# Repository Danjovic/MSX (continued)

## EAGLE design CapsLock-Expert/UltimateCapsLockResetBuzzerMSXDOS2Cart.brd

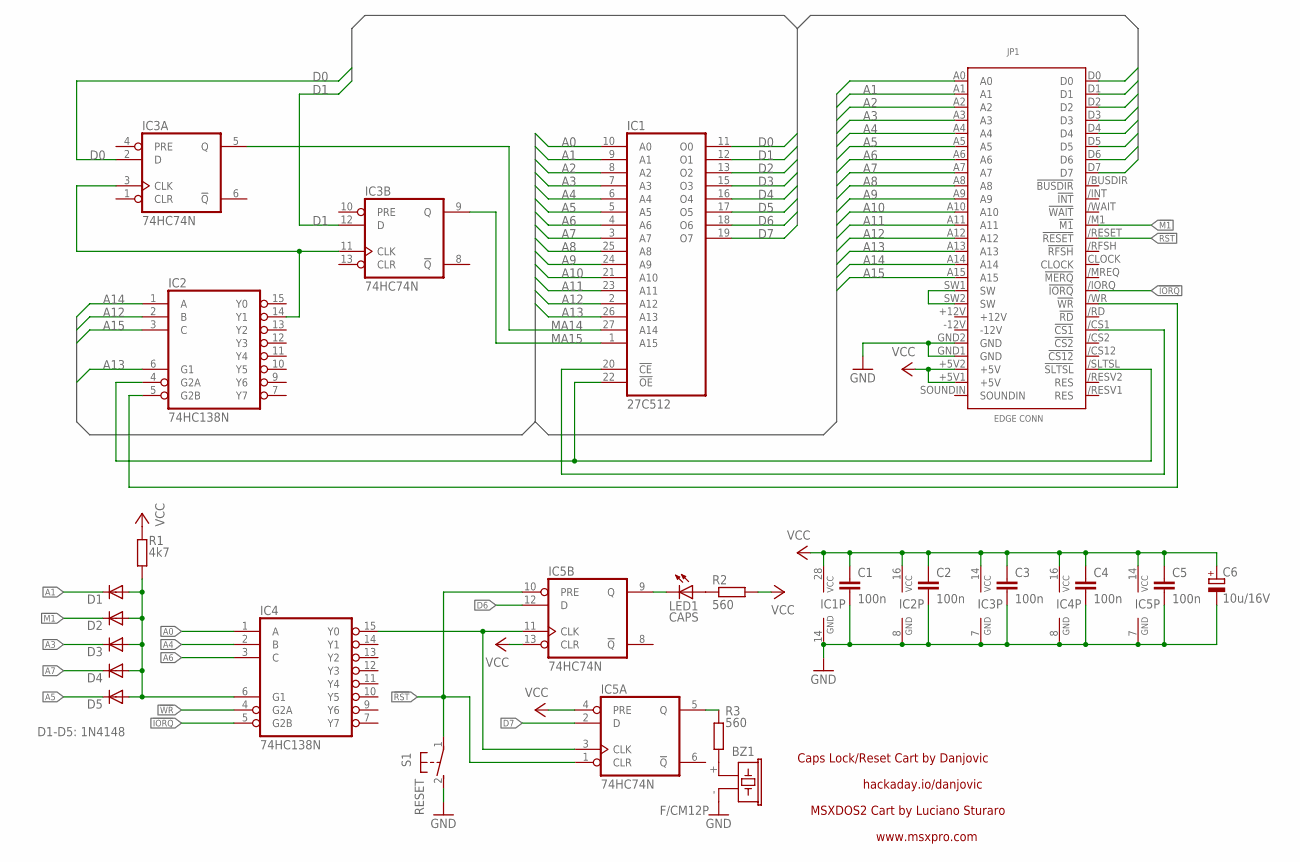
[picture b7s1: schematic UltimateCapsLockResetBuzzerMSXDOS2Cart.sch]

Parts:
BZ1: F/CM12P
C1, C2, C3, C4, C5: 100n; C050-030X075
C6: 10u/16V; E2,5-5
D1, D2, D3, D4, D5: DIODE-D-5; D-5
IC1: 27C512; DIL28
IC2, IC4: 74HC138N; DIL16
IC3, IC5: 74HC74N; DIL14
JP1: MSXCART; PATOLA-MSX
LED1: CAPS; Q62902-B155
R1: 4k7; 0204/5
R2, R3: 560; 0204/5
S1: RESET; B3F-31XX

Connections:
!CS1: IC1.20 (!CE), JP1./CS1 (!CS1)
!IORQ: IC4.5 (G2B), JP1./IORQ (!IORQ)
!M1: D2.C, JP1./M1 (!M1)
!RST: IC5.1 (CLR), IC5.10 (PRE), JP1./RESET (!RESET), S1.1
!SLTSL: IC1.22 (!OE), IC2.4 (G2A), JP1./SLTSL (!SLTSL)
!WR: IC2.5 (G2B), IC4.4 (G2A), JP1./WR (!WR)
A0: IC1.10 (A0), IC4.1 (A), JP1.A0
A1: D1.C, IC1.9 (A1), JP1.A1
A2: IC1.8 (A2), JP1.A2
A3: D3.C, IC1.7 (A3), JP1.A3
A4: IC1.6 (A4), IC4.2 (B), JP1.A4
A5: D5.C, IC1.5 (A5), JP1.A5
A6: IC1.4 (A6), IC4.3 (C), JP1.A6
A7: D4.C, IC1.3 (A7), JP1.A7
A8: IC1.25 (A8), JP1.A8
A9: IC1.24 (A9), JP1.A9
A10: IC1.21 (A10), JP1.A10
A11: IC1.23 (A11), JP1.A11
A12: IC1.2 (A12), IC2.2 (B), JP1.A12
A13: IC1.26 (A13), IC2.6 (G1), JP1.A13
A14: IC2.1 (A), JP1.A14
A15: IC2.3 (C), JP1.A15
D0: IC1.11 (O0), IC3.2 (D), JP1.D0
D1: IC1.12 (O1), IC3.12 (D), JP1.D1
D2: IC1.13 (O2), JP1.D2
D3: IC1.15 (O3), JP1.D3
D4: IC1.16 (O4), JP1.D4
D5: IC1.17 (O5), JP1.D5
D6: IC1.18 (O6), IC5.12 (D), JP1.D6
D7: IC1.19 (O7), IC5.2 (D), JP1.D7
GND: BZ1.- (2), C1.2, C2.2, C3.2, C4.2, C5.2, C6.-, IC1.14 (GND), IC2.8 (GND), IC3.7 (GND), IC4.8 (GND), IC5.7 (GND), JP1.GND1 (GND), JP1.GND2 (GND), S1.2 (S)
MA14: IC1.27 (A14), IC3.5 (Q)
MA15: IC1.1 (A15), IC3.9 (Q)
unnamed: IC5.9 (Q), LED1.K (C)
unnamed: IC2.14 (Y1), IC3.3 (CLK), IC3.11 (CLK)
unnamed: LED1.A, R2.1
unnamed: IC5.5 (Q), R3.1
unnamed: IC4.15 (Y0), IC5.3 (CLK), IC5.11 (CLK)
unnamed: BZ1.+ (1), R3.2
unnamed: D1.A, D2.A, D3.A, D4.A, D5.A, IC4.6 (G1), R1.2
SW1-2: JP1.SW1 (SW), JP1.SW2 (SW)
VCC: C1.1, C2.1, C3.1, C4.1, C5.1, C6.+, IC1.28 (VCC), IC2.16 (VCC), IC3.14 (VCC), IC4.16 (VCC), IC5.4 (PRE), IC5.13 (CLR), IC5.14 (VCC), JP1.+5V1 (+5V), JP1.+5V2 (+5V), R1.1, R2.2

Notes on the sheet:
MSXDOS2 Cart by Luciano Sturaro
www.msxpro.com
Caps Lock/Reset Cart by Danjovic
hackaday.io/danjovic
D1-D5: 1N4148

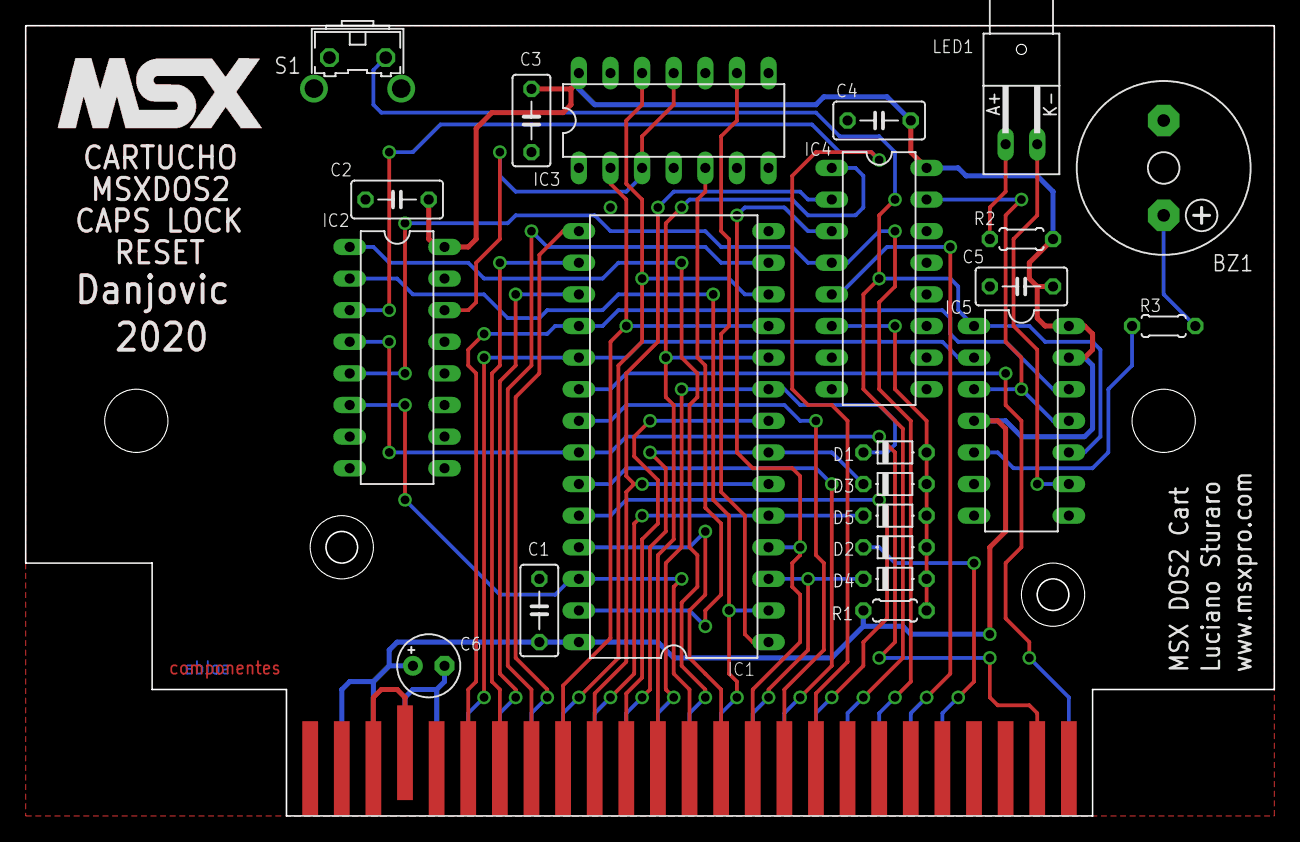
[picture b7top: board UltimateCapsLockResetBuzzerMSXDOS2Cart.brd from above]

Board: 2 copper layers, 100.3 x 63.5 mm, 23 parts (0 on the bottom side), 42 nets.

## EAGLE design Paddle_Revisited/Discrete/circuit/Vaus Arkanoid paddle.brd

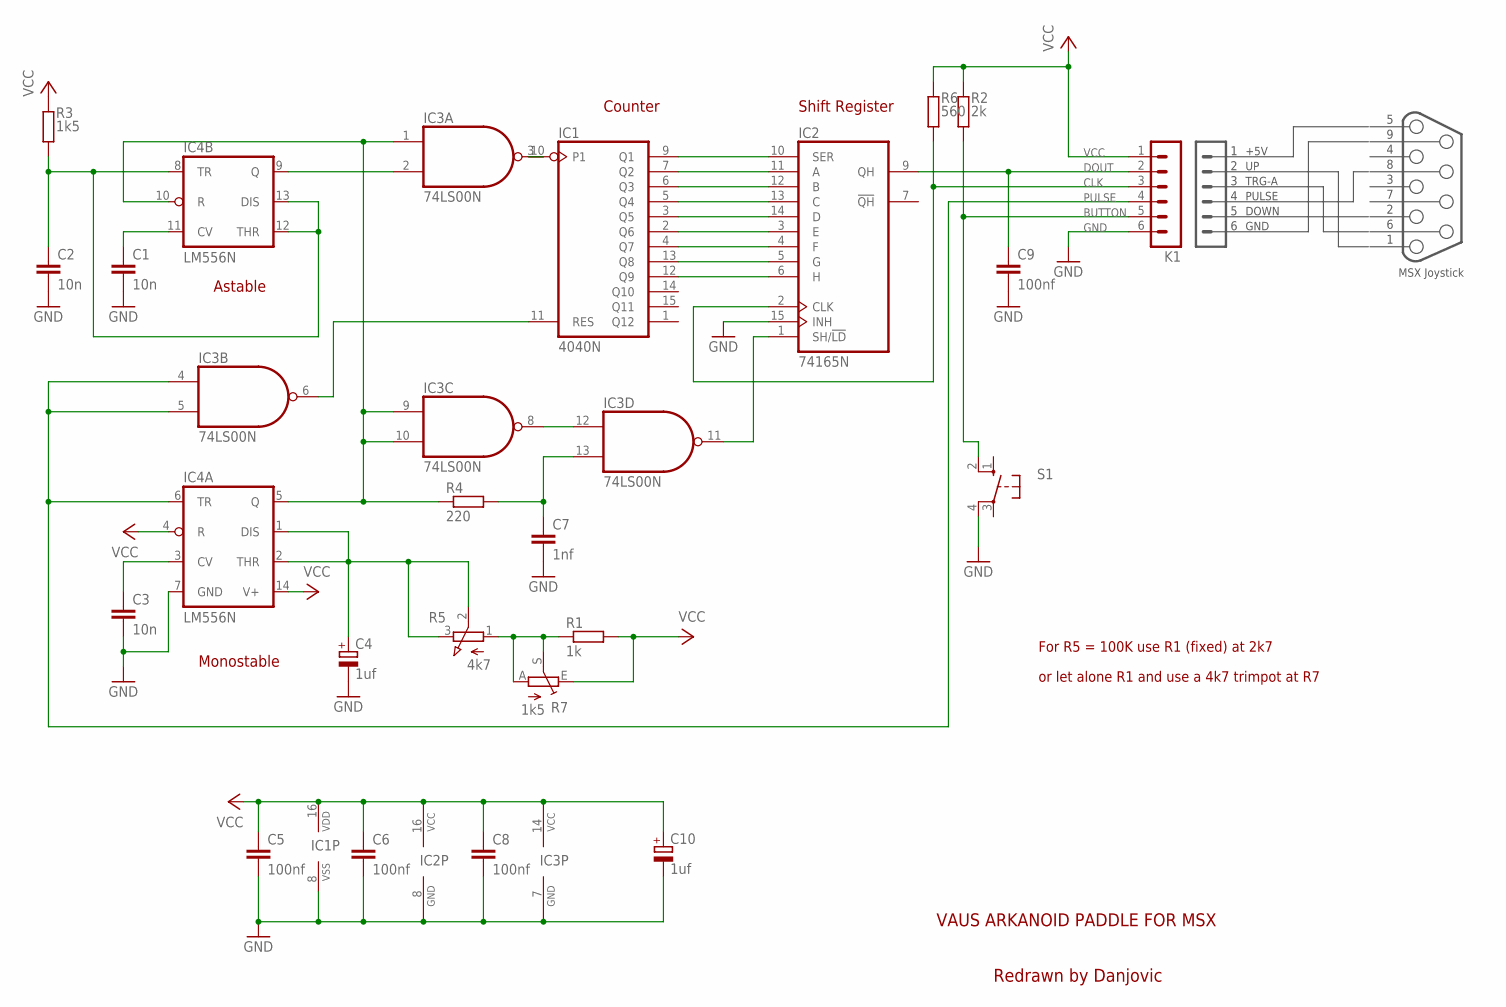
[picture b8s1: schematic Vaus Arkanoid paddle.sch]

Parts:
C1, C2, C3: 10n; C050-024X044
C4, C10: 1uf; E2-4
C5, C6, C8, C9: 100nf; C050-024X044
C7: 1nf; C050-024X044
IC1: 4040N; DIL16
IC2: 74165N; DIL16
IC3: 74LS00N; DIL14
IC4: LM556N; DIL14
K1: MA06-1
R1: 1k; 0207/7
R2: 2k; 0207/7
R3: 1k5; 0207/7
R4: 220; 0207/7
R5: 4k7; 3RP/1610N_THRU
R6: 560; 0207/7
R7: 1k5; CT6
S1: 40-XX; B3F-40XX

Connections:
BUTTON: K1.5, R2.1, S1.2 (S1)
CLK: IC2.2 (CLK), K1.3, R6.1
DOUT: C9.1, IC2.9 (QH), K1.2
GND: C1.2, C2.2, C3.2, C4.-, C5.2, C6.2, C7.2, C8.2, C9.2, C10.-, IC1.8 (VSS), IC2.8 (GND), IC2.15 (INH), IC3.7 (GND), IC4.7 (GND), K1.6, S1.4 (P1)
unnamed: IC2.1 (SH/!LD), IC3.11 (O)
unnamed: IC1.2 (Q6), IC2.3 (E)
unnamed: IC1.4 (Q7), IC2.4 (F)
unnamed: IC1.13 (Q8), IC2.5 (G)
unnamed: IC1.12 (Q9), IC2.6 (H)
unnamed: IC1.9 (Q1), IC2.10 (SER)
unnamed: IC1.7 (Q2), IC2.11 (A)
unnamed: IC1.6 (Q3), IC2.12 (B)
unnamed: IC1.5 (Q4), IC2.13 (C)
unnamed: IC1.3 (Q5), IC2.14 (D)
unnamed: IC3.8 (O), IC3.12 (I0)
unnamed: IC3.1 (I0), IC3.9 (I0), IC3.10 (I1), IC4.5 (Q), IC4.10 (R), R4.1
unnamed: C7.1, IC3.13 (I1), R4.2
unnamed: C2.1, IC4.8 (TR), IC4.12 (THR), IC4.13 (DIS), R3.1
unnamed: R1.1, R5.1 (A), R7.A, R7.S
unnamed: IC1.11 (RES), IC3.6 (O)
unnamed: IC1.10 (P1), IC3.3 (O)
unnamed: IC3.2 (I1), IC4.9 (Q)
unnamed: C4.+, IC4.1 (DIS), IC4.2 (THR), R5.2 (S), R5.3 (E)
unnamed: C1.1, IC4.11 (CV)
unnamed: C3.1, IC4.3 (CV)
PULSE: IC3.4 (I0), IC3.5 (I1), IC4.6 (TR), K1.4
VCC: C5.1, C6.1, C8.1, C10.+, IC1.16 (VDD), IC2.16 (VCC), IC3.14 (VCC), IC4.4 (R), IC4.14 (V+), K1.1, R1.2, R2.2, R3.2, R6.2, R7.E

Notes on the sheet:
DOWN
TRG-A
PULSE
+5V
GND
MSX Joystick
Monostable
Astable
Counter
Shift Register
VAUS ARKANOID PADDLE FOR MSX
Redrawn by Danjovic
For R5 = 100K use R1 (fixed) at 2k7
or let alone R1 and use a 4k7 trimpot at R7

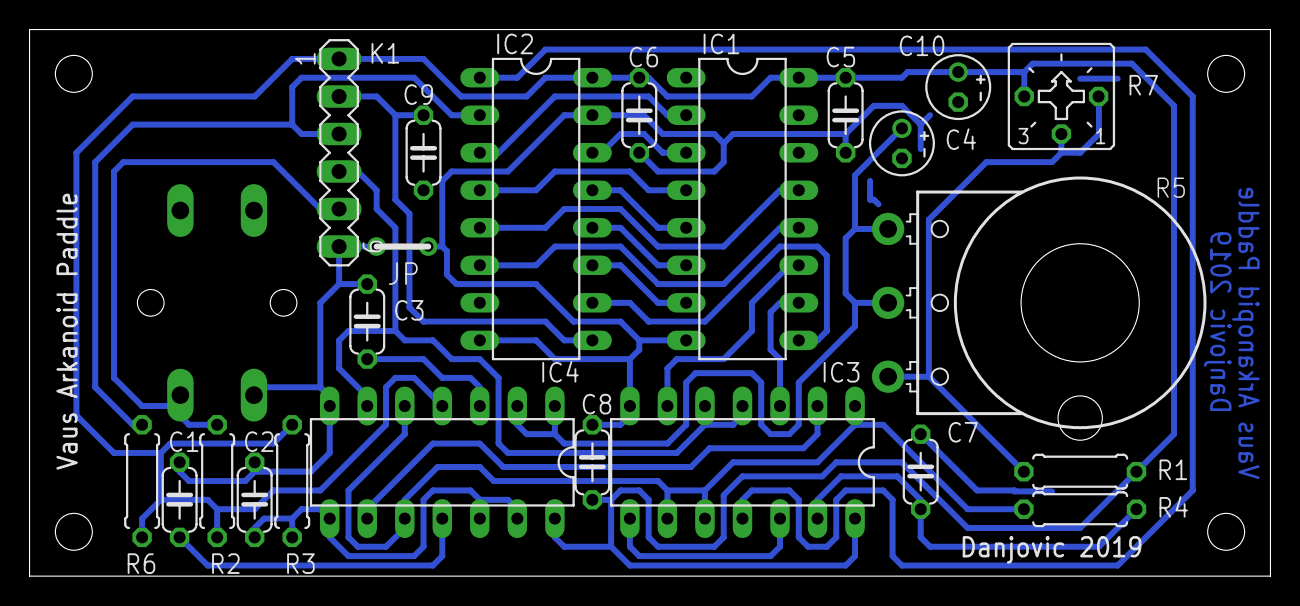
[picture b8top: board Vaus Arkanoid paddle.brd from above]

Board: 2 copper layers, 84.0 x 37.0 mm, 24 parts (1 on the bottom side), 27 nets.

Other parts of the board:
U$1: CP-011

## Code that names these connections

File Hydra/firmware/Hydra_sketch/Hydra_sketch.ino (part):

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
Arduino
/AVR    Function
 0/PD0  Nintendo 64 1 wire Clock/Data
 1/PD1  TXD for serial debug             
 2/PD2  MSX Pulse input (INT0)             
 3/PD3  Dualshock ATT / SNES Latch / Shift Register Latch (Sega) 
 4/PD4  Dualshock CLK / SNES Clock / Shift Register Clock (Sega) 
 5/PD5  Dualshock CMD /            / Sega SELECT    
 6/PD6  Dualshock DATA      
 7/PD7  Dualshock ACK     
 8/PB0  MSX UP    (output)           
 9/PB1  MSX DOWN  (output)             
10/PB2  MSX LEFT  (output)             
11/PB3  MSX RIGHT (output)             
12/PB4  MSX TRGA  (output)            
13/PB5  MSX TRGB  (output)             
A0/PC0  Shift Register Data (Sega)   
A1/PC1  SNES Data   
A2/PC2  Mouse DAT           
A3/PC3  Mouse CLK           
A4/PC4  OLED display I2C SCL / WII nunchuck I2C SCL       
A5/PC5  OLED display I2C SDA / WII nunchuck I2C SDA      
*/
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#define mdTRACKBALL         5  // 5 = Trackball
#define mdTOUCHPAD          6  // 6 = Touchpad

#define JoyPin1  8 // PB0 UP
#define JoyPin2  9 // PB1 DOWN
#define JoyPin3 10 // PB2 LEFT
#define JoyPin4 11 // PB3 RIGHT
#define JoyPin6 12 // PB4 TRIGGER A
#define JoyPin7 13 // PB5 TRIGGER B
#define JoyPin8  2 // PD2 PULSE
long time; // No C


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// Nintendo 64 device library by NicoHood
// https://www.github.com/NicoHood/Nintendo
#include "Nintendo.h"
#define N64 0   // PD0
#define GCUBE 7 // PD7
CN64Controller N64Controller(N64);// Define a N64 Controller
CGamecubeController GamecubeController(GCUBE);// Define a Gamecube Controller

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#define MSX_PORT PORTB
#define MSX_DDR  DDRB

#define MSX_UP    0  // PB0
#define MSX_DOWN  1  // PB1
#define MSX_LEFT  2  // PB2
#define MSX_RIGHT 3  // PB3
#define MSX_TRGA  4  // PB4
#define MSX_TRGB  5  // PB5

//uint8_t msx_buttons  = 0xff;  // no button pressed
static volatile uint8_t msx_paddle_1_2   = 0; // Pin 1 - UP      
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  temp = ps2x.readType();

  if (temp==1) {  // Dualshock
    ps2x.read_gamepad(false, 0); //read controller and set large motor to spin at 'vibrate' speed
    if(ps2x.Button(PSB_GREEN)) return DUALSHOCK;  // triangle is A button 
    
    } else if (temp==2) {  // Guitar
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
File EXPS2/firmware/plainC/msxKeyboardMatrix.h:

//    _____  _____  ___   _____
//   | __\ \/ / _ \/ __| / /_  )
//   | _| >  <|  _/\__ \/ / / /
//   |___/_/\_\_|  |___/_/ /___|
//
//   Teclado PS/2 externo para Expert XP800

// Conexao dos pinos do AVR com a PPI
// AVR interface pin assignment to the PPI

// AVR  PPI

// PC0  PC0   /   sel A
// PC1  PC1   /   sel B
// PC2  PC2   /   sel C
// PC3  PC3   /   sel D

// PD0  PB5   /   X5
// PD1  PB0   /   X0
// PD2  PB6   /   X6
// PD3  PB2   /   X2
// PD4  PB7   /   X7
// PD5  PB4   /   X4
// PD6  PB1   /   X1
// PD7  PB3   /   X3

/*
SH  ROW[0..10] COL [0..7]

    7     6     5     4     3     2     1     0    BIT
 +-----------------------------------------------+
 |SHIFT|       ROW [0..10]     |    COL[0..7]    |
 +-----------------------------------------------+


    7     6     5     4     3     2     1     0    BIT
 +-----------------------------------------------+
 |  7  |  5  |  6  |  4  |  3  |  2  |  1  |  0  |   Row 0
 +-----+-----+-----+-----+-----+-----+-----+-----|
 |  ;  |  [  |  ]  |  \  |  =  |  -  |  9  |  8  |   Row 1
 +-----+-----+-----+-----+-----+-----+-----+-----|
 |  B  |  |  |  A  |  /  |  .  |  ,  |  `  |  '  |   Row 2
 +-----+-----+-----+-----+-----+-----+-----+-----|
 |  J  |  H  |  I  |  G  |  F  |  E  |  D  |  C  |   Row 3
 +-----+-----+-----+-----+-----+-----+-----+-----|
 |  R  |  P  |  Q  |  O  |  N  |  M  |  L  |  K  |   Row 4
 +-----+-----+-----+-----+-----+-----+-----+-----|
 |  Z  |  X  |  Y  |  W  |  V  |  U  |  T  |  S  |   Row 5
 +-----+-----+-----+-----+-----+-----+-----+-----|
 | F3  | F1  | F2  |CODE | CAP |GRAPH|CTRL |SHIFT|   Row 6
 +-----+-----+-----+-----+-----+-----+-----+-----|
 | CR  | BS  | SEL |STOP | TAB | ESC | F5  | F4  |   Row 7
 +-----+-----+-----+-----+-----+-----+-----+-----|
 |RIGHT| UP  |DOWN |LEFT | DEL | INS |HOME |SPACE|   Row 8
 +-----+-----+-----+-----+-----+-----+-----+-----|
 | KP4 | KP2 | KP2 | KP1 | KP0 |NUM/ |NUM+ |NUM* |   Row 9
 +-----+-----+-----+-----+-----+-----+-----+-----|
 |  .  |  -  |  ,  | KP9 | KP8 | KP7 | KP6 | KP5 |   Row 10
 +-----------------------------------------------+
    7     5     6     4     3     2     1     0       Column

*/

// Mapa das linhas de selecao da PPI
// PPI selection line mapping
//      line bit
#define selA  0
#define selB  1
#define selC  2
#define selD  3


#define row0  ( (0<<selD)|(0<<selC)|(0<<selB)|(0<<selA) ) <<3
#define row1  ( (0<<selD)|(0<<selC)|(0<<selB)|(1<<selA) ) <<3
#define row2  ( (0<<selD)|(0<<selC)|(1<<selB)|(0<<selA) ) <<3
#define row3  ( (0<<selD)|(0<<selC)|(1<<selB)|(1<<selA) ) <<3
#define row4  ( (0<<selD)|(1<<selC)|(0<<selB)|(0<<selA) ) <<3
#define row5  ( (0<<selD)|(1<<selC)|(0<<selB)|(1<<selA) ) <<3
#define row6  ( (0<<selD)|(1<<selC)|(1<<selB)|(0<<selA) ) <<3
#define row7  ( (0<<selD)|(1<<selC)|(1<<selB)|(1<<selA) ) <<3
#define row8  ( (1<<selD)|(0<<selC)|(0<<selB)|(0<<selA) ) <<3
#define row9  ( (1<<selD)|(0<<selC)|(0<<selB)|(1<<selA) ) <<3
#define rowA  ( (1<<selD)|(0<<selC)|(1<<selB)|(0<<selA) ) <<3
#define rowB  ( (1<<selD)|(0<<selC)|(1<<selB)|(1<<selA) ) <<3
#define rowC  ( (1<<selD)|(1<<selC)|(0<<selB)|(0<<selA) ) <<3
#define rowD  ( (1<<selD)|(1<<selC)|(0<<selB)|(1<<selA) ) <<3
#define rowE  ( (1<<selD)|(1<<selC)|(1<<selB)|(0<<selA) ) <<3
#define rowF  ( (1<<selD)|(1<<selC)|(1<<selB)|(1<<selA) ) <<3


// Posicao das bits das colunas (teclas)
// Column position bit mapping (keys)
//   column  bit
#define col0  5
#define col1  0
#define col2  6
#define col3  2
#define col4  7
#define col5  4
#define col6  1
#define col7  3


//  SHIFT Position in Matrx
#define LIN_SHIFT 6
#define COL_SHIFT col0


#define _NONE          0x7F
#define _SH            0x80

#define _0            ( row0 | col0 )
#define _1            ( row0 | col1 )
#define _2            ( row0 | col2 )
#define _3            ( row0 | col3 )
#define _4            ( row0 | col4 )
#define _5            ( row0 | col5 )
#define _6            ( row0 | col6 )
#define _7            ( row0 | col7 )

#define _8            ( row1 | col0 )
#define _9            ( row1 | col1 )
#define _MINUS        ( row1 | col2 )
#define _EQUAL        ( row1 | col3 )
#define _OPENBRACKET  ( row1 | col4 )
#define _ACUTE        ( row1 | col5 )
#define _OPENKEY      ( row1 | col6 )
#define _TILDE        ( row1 | col7 )

#define _ASTERISK     ( row2 | col0 )
#define _CCEDIL       ( row2 | col1 )
#define _COMMA        ( row2 | col2 )
#define _DOT          ( row2 | col3 )
#define _SEMICOLON    ( row2 | col4 )
#define _SLASH        ( row2 | col5 )
#define _A            ( row2 | col6 )
#define _B            ( row2 | col7 )

#define _C            ( row3 | col0 )
#define _D            ( row3 | col1 )
#define _E            ( row3 | col2 )
#define _F            ( row3 | col3 )
#define _G            ( row3 | col4 )
#define _H            ( row3 | col5 )
#define _I            ( row3 | col6 )
#define _J            ( row3 | col7 )

#define _K            ( row4 | col0 )
#define _L            ( row4 | col1 )
#define _M            ( row4 | col2 )
#define _N            ( row4 | col3 )
#define _O            ( row4 | col4 )
#define _P            ( row4 | col5 )
#define _Q            ( row4 | col6 )
#define _R            ( row4 | col7 )

#define _S            ( row5 | col0 )
#define _T            ( row5 | col1 )
#define _U            ( row5 | col2 )
#define _V            ( row5 | col3 )
#define _W            ( row5 | col4 )
#define _X            ( row5 | col5 )
#define _Y            ( row5 | col6 )
#define _Z            ( row5 | col7 )

#define _SHIFT        ( row6 | col0 )
#define _CONTROL      ( row6 | col1 )
#define _GRAPH        ( row6 | col2 )
#define _CAPS         ( row6 | col3 )
#define _CODE         ( row6 | col4 )
#define _F1           ( row6 | col5 )
#define _F2           ( row6 | col6 )
#define _F3           ( row6 | col7 )

#define _F4           ( row7 | col0 )
#define _F5           ( row7 | col1 )
#define _ESC          ( row7 | col2 )
#define _TAB          ( row7 | col3 )
#define _STOP         ( row7 | col4 )
#define _BACKSPACE    ( row7 | col5 )
#define _SELECT       ( row7 | col6 )
#define _ENTER        ( row7 | col7 )

#define _SPACE        ( row8 | col0 )
#define _HOME         ( row8 | col1 )
#define _INSERT       ( row8 | col2 )
#define _DELETE       ( row8 | col3 )
#define _LEFT         ( row8 | col4 )
#define _UP           ( row8 | col5 )
#define _DOWN         ( row8 | col6 )
#define _RIGHT        ( row8 | col7 )

#define _KPPLUS       ( row9 | col0 )    
#define _KPMINUS      ( row9 | col1 )    
#define _KPTIMES      ( row9 | col2 )    
#define _KPSLASH      ( row9 | col3 )    

#define _KP1          ( _NONE       )    
#define _KP2          ( _NONE       )    
#define _KP3          ( _NONE       )    
#define _KP4          ( _NONE       )    

#define _KP5          ( _NONE       )    
#define _KP6          ( _NONE       )    
#define _KP7          ( _NONE       )    
#define _KP8          ( _NONE       )   
#define _KP9          ( _NONE       )       
#define _KPCOMMA      ( _NONE       )    
#define _KPDOT        ( _NONE       )    

// Shifted
#define _F6           ( _SH + _F1 )        // F6
#define _F7           ( _SH + _F2 )        // F7
#define _F8           ( _SH + _F3 )        // F8
#define _F9           ( _SH + _F4 )        // F9
#define _F10          ( _SH + _F5 )        // F10

#define _EXCLAMATION  ( _SH + _1  )         // !
#define _QUOTE        ( _SH + _2  )         // "
#define _NUMBER       ( _SH + _3  )         // #
#define _DOLLAR       ( _SH + _4  )         // $
#define _PERCENT      ( _SH + _5  )         // %
#define _POWER        ( _SH + _6  )         // ^
#define _AMPERSAND    ( _SH + _7  )         // &
#define _APOSTROPHE   ( _SH + _8  )         // '
#define _OPENBRACE    ( _SH + _9  )         // (
#define _CLOSEBRACE   ( _SH + _0  )         // )

#define _AT           ( _SH + _ASTERISK   ) // @
#define _UNDERSCORE   ( _SH + _MINUS      ) // _
#define _PLUS         ( _SH + _EQUAL      ) // +
#define _CLOSEKEY     ( _SH + _OPENKEY    ) // }

#define _GRAVE        ( _SH + _ACUTE      ) // `
#define _CLOSEBRACKET ( _SH + _OPENBRACKET) // ]
#define _CIRCUMFLEX   ( _SH + _TILDE      ) // ^

#define _LESSTHAN     ( _SH + _COMMA      ) // <
#define _GREATERTHAN  ( _SH + _DOT        ) // >
#define _COLON        ( _SH + _SEMICOLON  ) // :
#define _QUESTION     ( _SH + _SLASH      ) // ?

#define _PIPE         (  _NONE )

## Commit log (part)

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2016-10-28 Basic Release
2016-12-05 Add RESET switch and alternate LED/RESET mounting positons
2016-12-05 wrong name
2016-12-05 Added Reset Button
2016-12-05 useless file
2016-12-05 outdated
2017-12-18 I2C stuff for joystick port
2018-05-16 Repository created
2018-05-22 Added Schematics Folder, added HB8000 schematic redrawn
2018-09-29 J2C code captured from MSX
2019-06-08 Added RF modulator, corrected main board schematic
    Added rebuilt schematics of RF modulator, corrected supply voltage for RF modulator on main board (was 5V instead of 12V) and updated library with LM1889 modulator
2019-06-08 Added RF modulator, updated main board and library
    Added rebuilt schematics of RF modulator, corrected supply voltage for RF modulator on main board (was 5V instead of 12V) and updated library with LM1889 modulator
2019-07-02 added orpheus files
2019-07-02 move files to folder
2019-07-08 upload files - NOT TESTED ON REAL HARDWARE SO FAR
2019-08-11 added N64toMSX subproject
2019-08-12 test version, partially functional
2019-08-12 cleanup
2019-08-12 added project, partially working
2019-08-13 Button logic OK, Autofire not ready yet
2019-08-15 Timeout/task interleaving mechanism behaving as expected
2019-08-18 First NSX-64 working release
2019-08-18 cleanup, conditionals on debug code
2019-08-22 upload of files, not tested!
2019-08-24 Cleanup and organization of some directories
2019-08-24 Added Joystick port Video Card project
2019-09-07 MSX tested working, SMS partially verified.
2020-02-23 Updated component values
2020-03-30 Upload of Files
2020-04-02 Eliminated interference caused by glitches in PULSE line
2020-04-05 Enhanced Version
    Enhanced version, support Arduino UNO, Nano and Digispark, provides both Arkanoid and MSX Standard paddle.
2020-04-05 Added documentation, reorganized directories
2020-04-05 Added Pullup resistor
2020-04-05 Enhanced image
2020-04-05 Enhanded Image
2020-08-07 Added Zorax Logo
2020-08-07 corrected X
2020-11-23 Added Ultimate Caps Lock Reset MSXDOS2 cart PCB Layout
2020-11-23 Corrected Caps Lock LED activation (in LOW)
2020-11-23 Added a buzzer
2020-12-29 Adicionada placa RF Hotbit Preto, contribuição de Fábio Belavenuto.
2021-04-10 Arduino code ported to Plain C
2021-05-23 Updated Single Sided Board
2021-05-30 Corrected PS2 clock/dat pin assignment to reflect PCB
2021-10-20 Added FA-32 cassete adapter schematic
2021-10-20 added schematic in pdf
2021-10-22 Added PCB for Hammond 1593j box
    With two options for transistor and for relay
2021-10-29 Added Cable for board CA3427-3 (FA32 BR version)
2021-10-29 Update board, added images
2021-10-30 Updated files
2021-12-13 very early release
2022-01-02 untested, just uploaded
2022-10-06 added joystick type to return byte in B register
2022-10-07 bug fix
2022-10-10 Adeed DE-9 version, pullup resitors on data lines
2022-10-10 updated schematics
2022-10-11 corrected clock ringing
2022-11-05 Muhonmourn3 patch (untested)
2022-11-06 changed patch start address
2022-11-06 added patch
2022-11-06 changed to use TAP on port 1
2022-11-06 fixed bug tap2 left
2022-11-13 Added ROM version of patched Muhonmourn3
2022-11-15 added splash screen and no-ram screen
2022-11-15 fixed problem with subslots
2023-05-19 Added Touch Digitizer project
2023-12-26 Add files via upload
    upload only, code not debugged
2024-04-02 debugged
2024-11-07 added ScanJ2c
2025-02-26 Added Dev Ram Cart Project
2025-02-27 code cleanup
2025-03-04 Improved Open Collector emulation, fixed compilation with TinyCore
2025-03-29 fixed name of signals on printer port
